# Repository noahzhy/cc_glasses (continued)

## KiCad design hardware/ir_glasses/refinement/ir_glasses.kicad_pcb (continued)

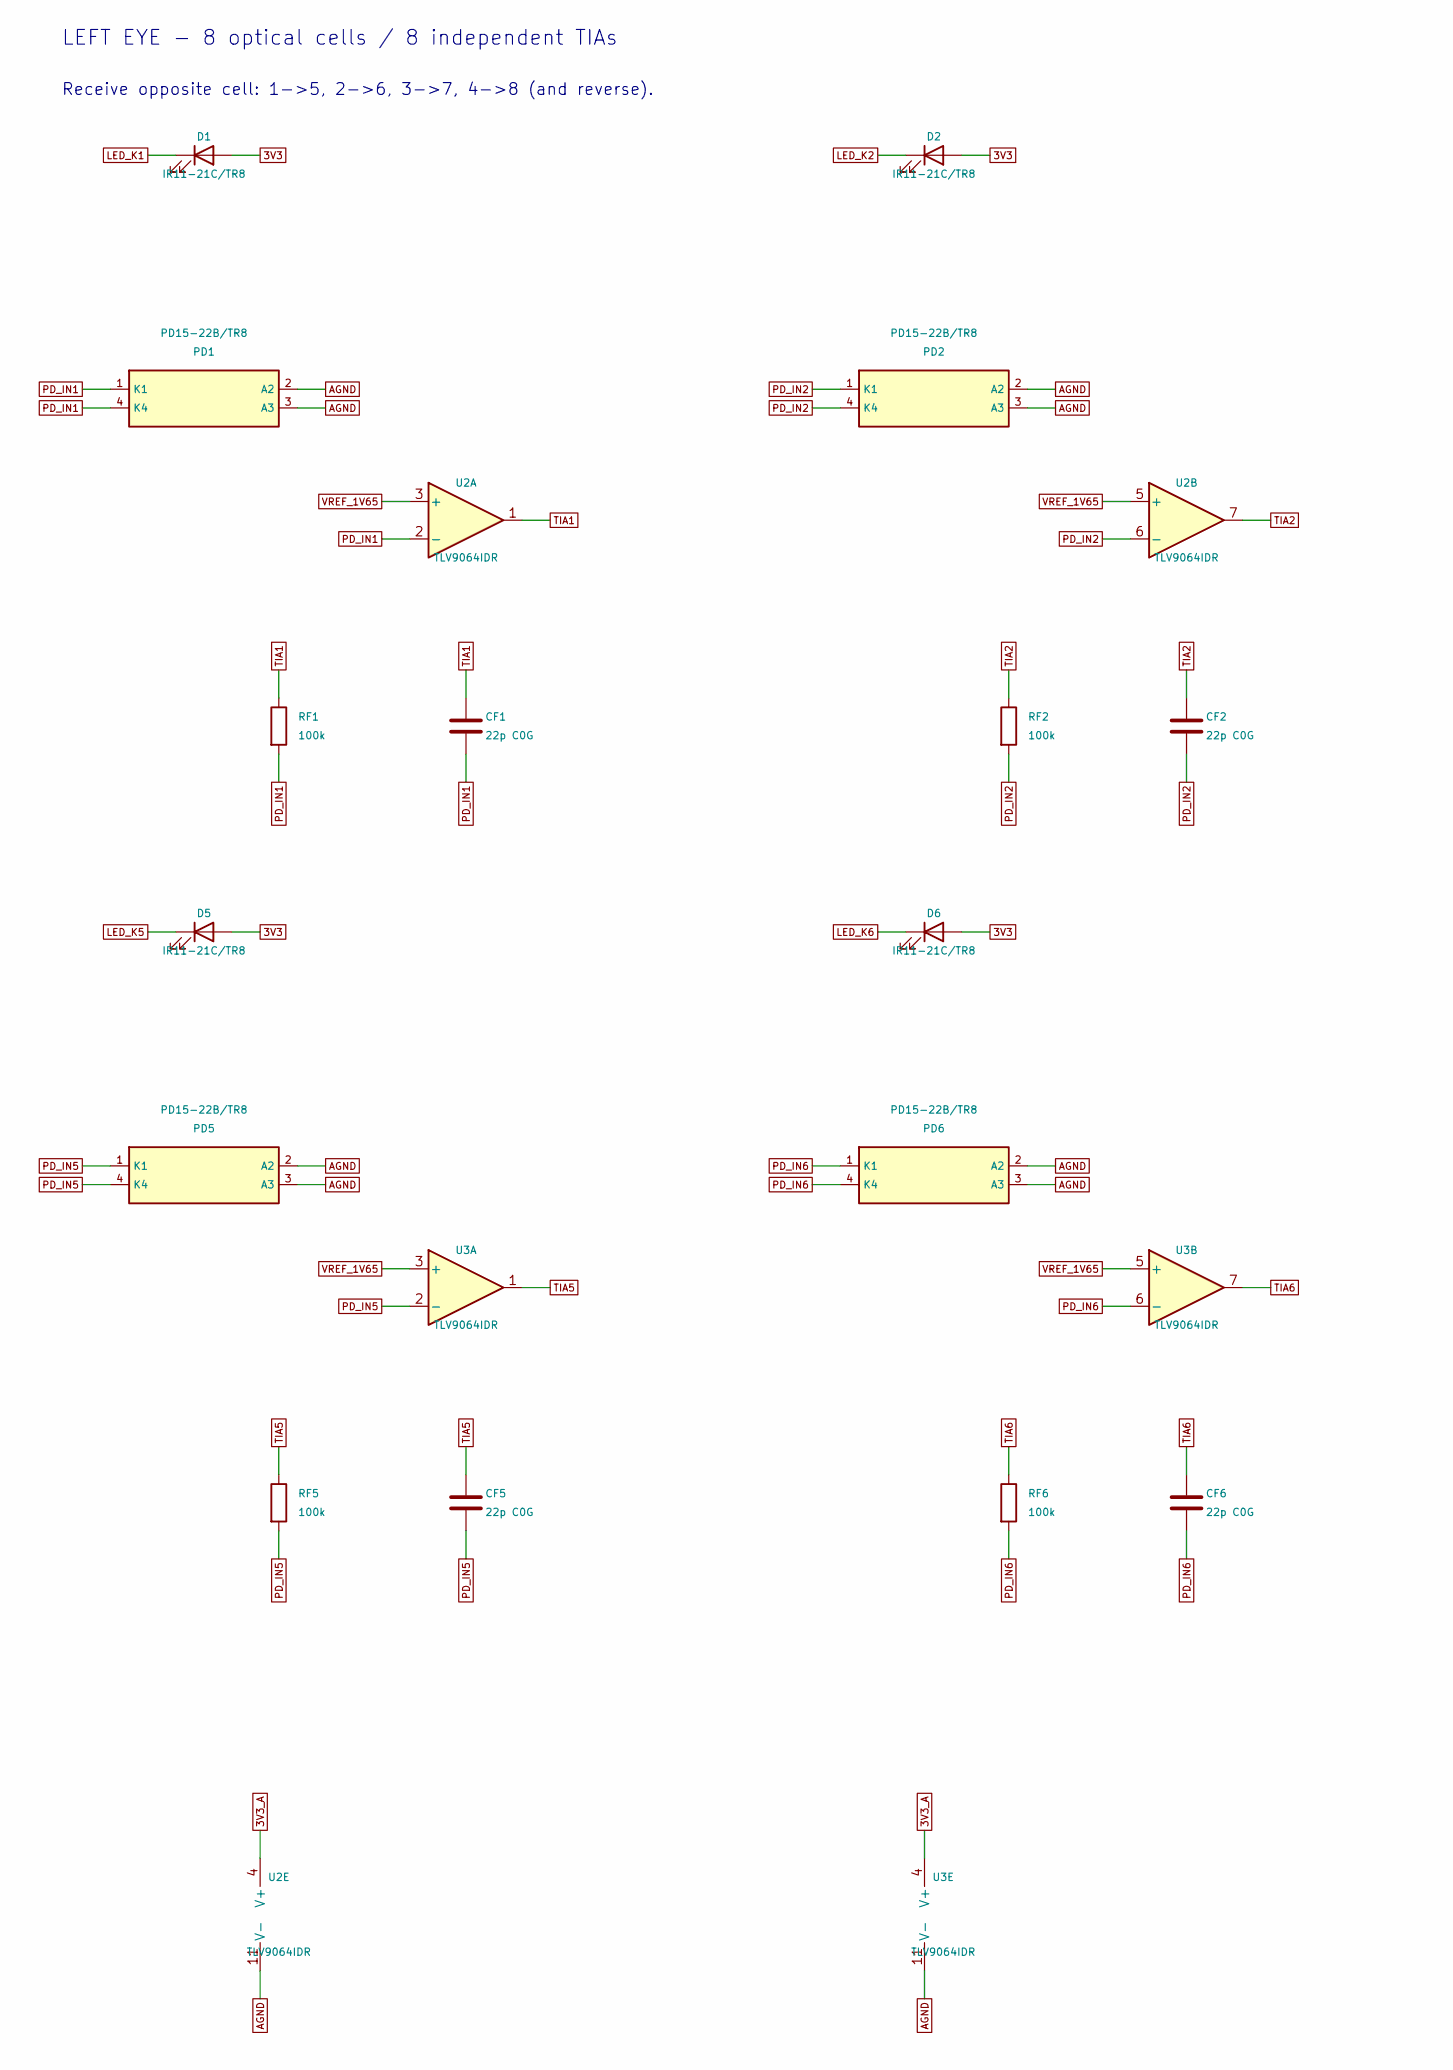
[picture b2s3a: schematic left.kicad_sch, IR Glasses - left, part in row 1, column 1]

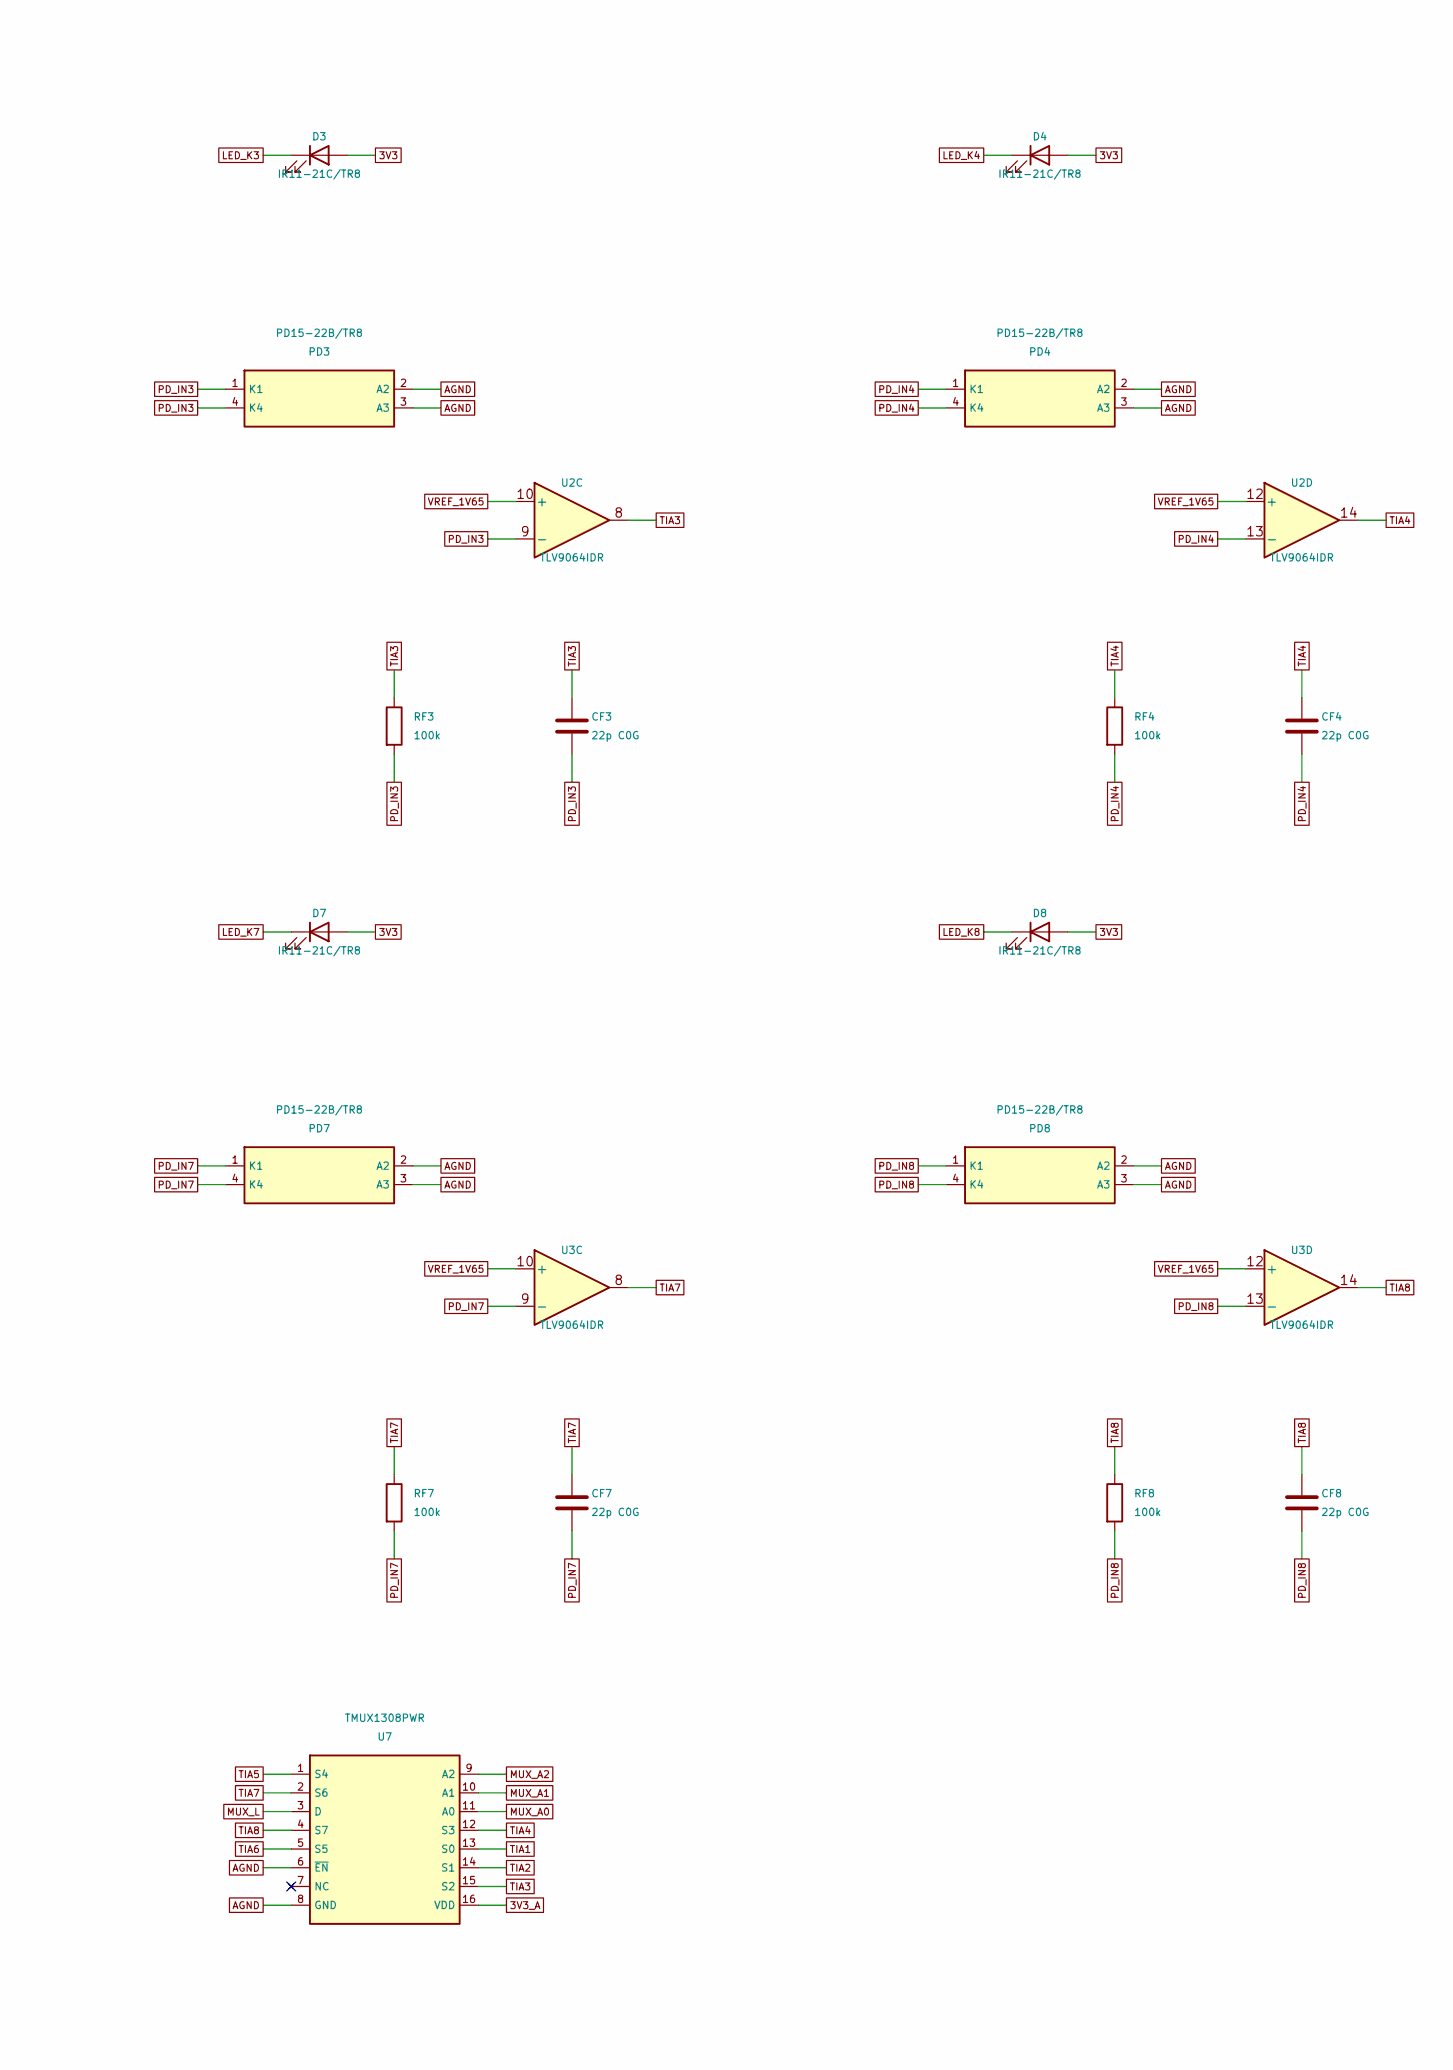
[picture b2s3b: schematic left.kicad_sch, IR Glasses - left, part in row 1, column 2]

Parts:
CF1, CF2, CF3, CF4, CF5, CF6, CF7, CF8: 22p C0G; C_0402_1005Metric
D1, D2, D3, D4, D5, D6, D7, D8: IR11-21C/TR8; Everlight_IR11_21C
PD1, PD2, PD3, PD4, PD5, PD6, PD7, PD8: PD15-22B/TR8; Everlight_PD15_22B
RF1, RF2, RF3, RF4, RF5, RF6, RF7, RF8: 100k; R_0402_1005Metric
U2, U3: TLV9064IDR; SOIC-14_3.9x8.7mm_P1.27mm
U7: TMUX1308PWR; TSSOP-16_4.4x5mm_P0.65mm

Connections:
3V3: D1.1 (A), D2.1 (A), D3.1 (A), D4.1 (A), D5.1 (A), D6.1 (A), D7.1 (A), D8.1 (A); also elsewhere on the board
3V3_A: U2.4 (V+), U3.4 (V+), U7.16 (VDD); also elsewhere on the board
AGND: PD1.2 (A2), PD1.3 (A3), PD2.2 (A2), PD2.3 (A3), PD3.2 (A2), PD3.3 (A3), PD4.2 (A2), PD4.3 (A3), PD5.2 (A2), PD5.3 (A3), PD6.2 (A2), PD6.3 (A3), PD7.2 (A2), PD7.3 (A3), PD8.2 (A2), PD8.3 (A3), U2.11 (V-), U3.11 (V-), U7.6 (~EN), U7.8 (GND); also elsewhere on the board
LED_K1: D1.2 (K); also elsewhere on the board
LED_K2: D2.2 (K); also elsewhere on the board
LED_K3: D3.2 (K); also elsewhere on the board
LED_K4: D4.2 (K); also elsewhere on the board
LED_K5: D5.2 (K); also elsewhere on the board
LED_K6: D6.2 (K); also elsewhere on the board
LED_K7: D7.2 (K); also elsewhere on the board
LED_K8: D8.2 (K); also elsewhere on the board
MUX_A0: U7.11 (A0); also elsewhere on the board
MUX_A1: U7.10 (A1); also elsewhere on the board
MUX_A2: U7.9 (A2); also elsewhere on the board
MUX_L: U7.3 (D); also elsewhere on the board
PD_IN1: CF1.2, PD1.1 (K1), PD1.4 (K4), RF1.2, U2.2 (-)
PD_IN2: CF2.2, PD2.1 (K1), PD2.4 (K4), RF2.2, U2.6 (-)
PD_IN3: CF3.2, PD3.1 (K1), PD3.4 (K4), RF3.2, U2.9 (-)
PD_IN4: CF4.2, PD4.1 (K1), PD4.4 (K4), RF4.2, U2.13 (-)
PD_IN5: CF5.2, PD5.1 (K1), PD5.4 (K4), RF5.2, U3.2 (-)
PD_IN6: CF6.2, PD6.1 (K1), PD6.4 (K4), RF6.2, U3.6 (-)
PD_IN7: CF7.2, PD7.1 (K1), PD7.4 (K4), RF7.2, U3.9 (-)
PD_IN8: CF8.2, PD8.1 (K1), PD8.4 (K4), RF8.2, U3.13 (-)
TIA1: CF1.1, RF1.1, U2.1, U7.13 (S0)
TIA2: CF2.1, RF2.1, U2.7, U7.14 (S1)
TIA3: CF3.1, RF3.1, U2.8, U7.15 (S2)
TIA4: CF4.1, RF4.1, U2.14, U7.12 (S3)
TIA5: CF5.1, RF5.1, U3.1, U7.1 (S4)
TIA6: CF6.1, RF6.1, U3.7, U7.5 (S5)
TIA7: CF7.1, RF7.1, U3.8, U7.2 (S6)
TIA8: CF8.1, RF8.1, U3.14, U7.4 (S7)
VREF_1V65: U2.3 (+), U2.5 (+), U2.10 (+), U2.12 (+), U3.3 (+), U3.5 (+), U3.10 (+), U3.12 (+); also elsewhere on the board

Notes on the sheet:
LEFT EYE - 8 optical cells / 8 independent TIAs
Receive opposite cell: 1->5, 2->6, 3->7, 4->8 (and reverse).

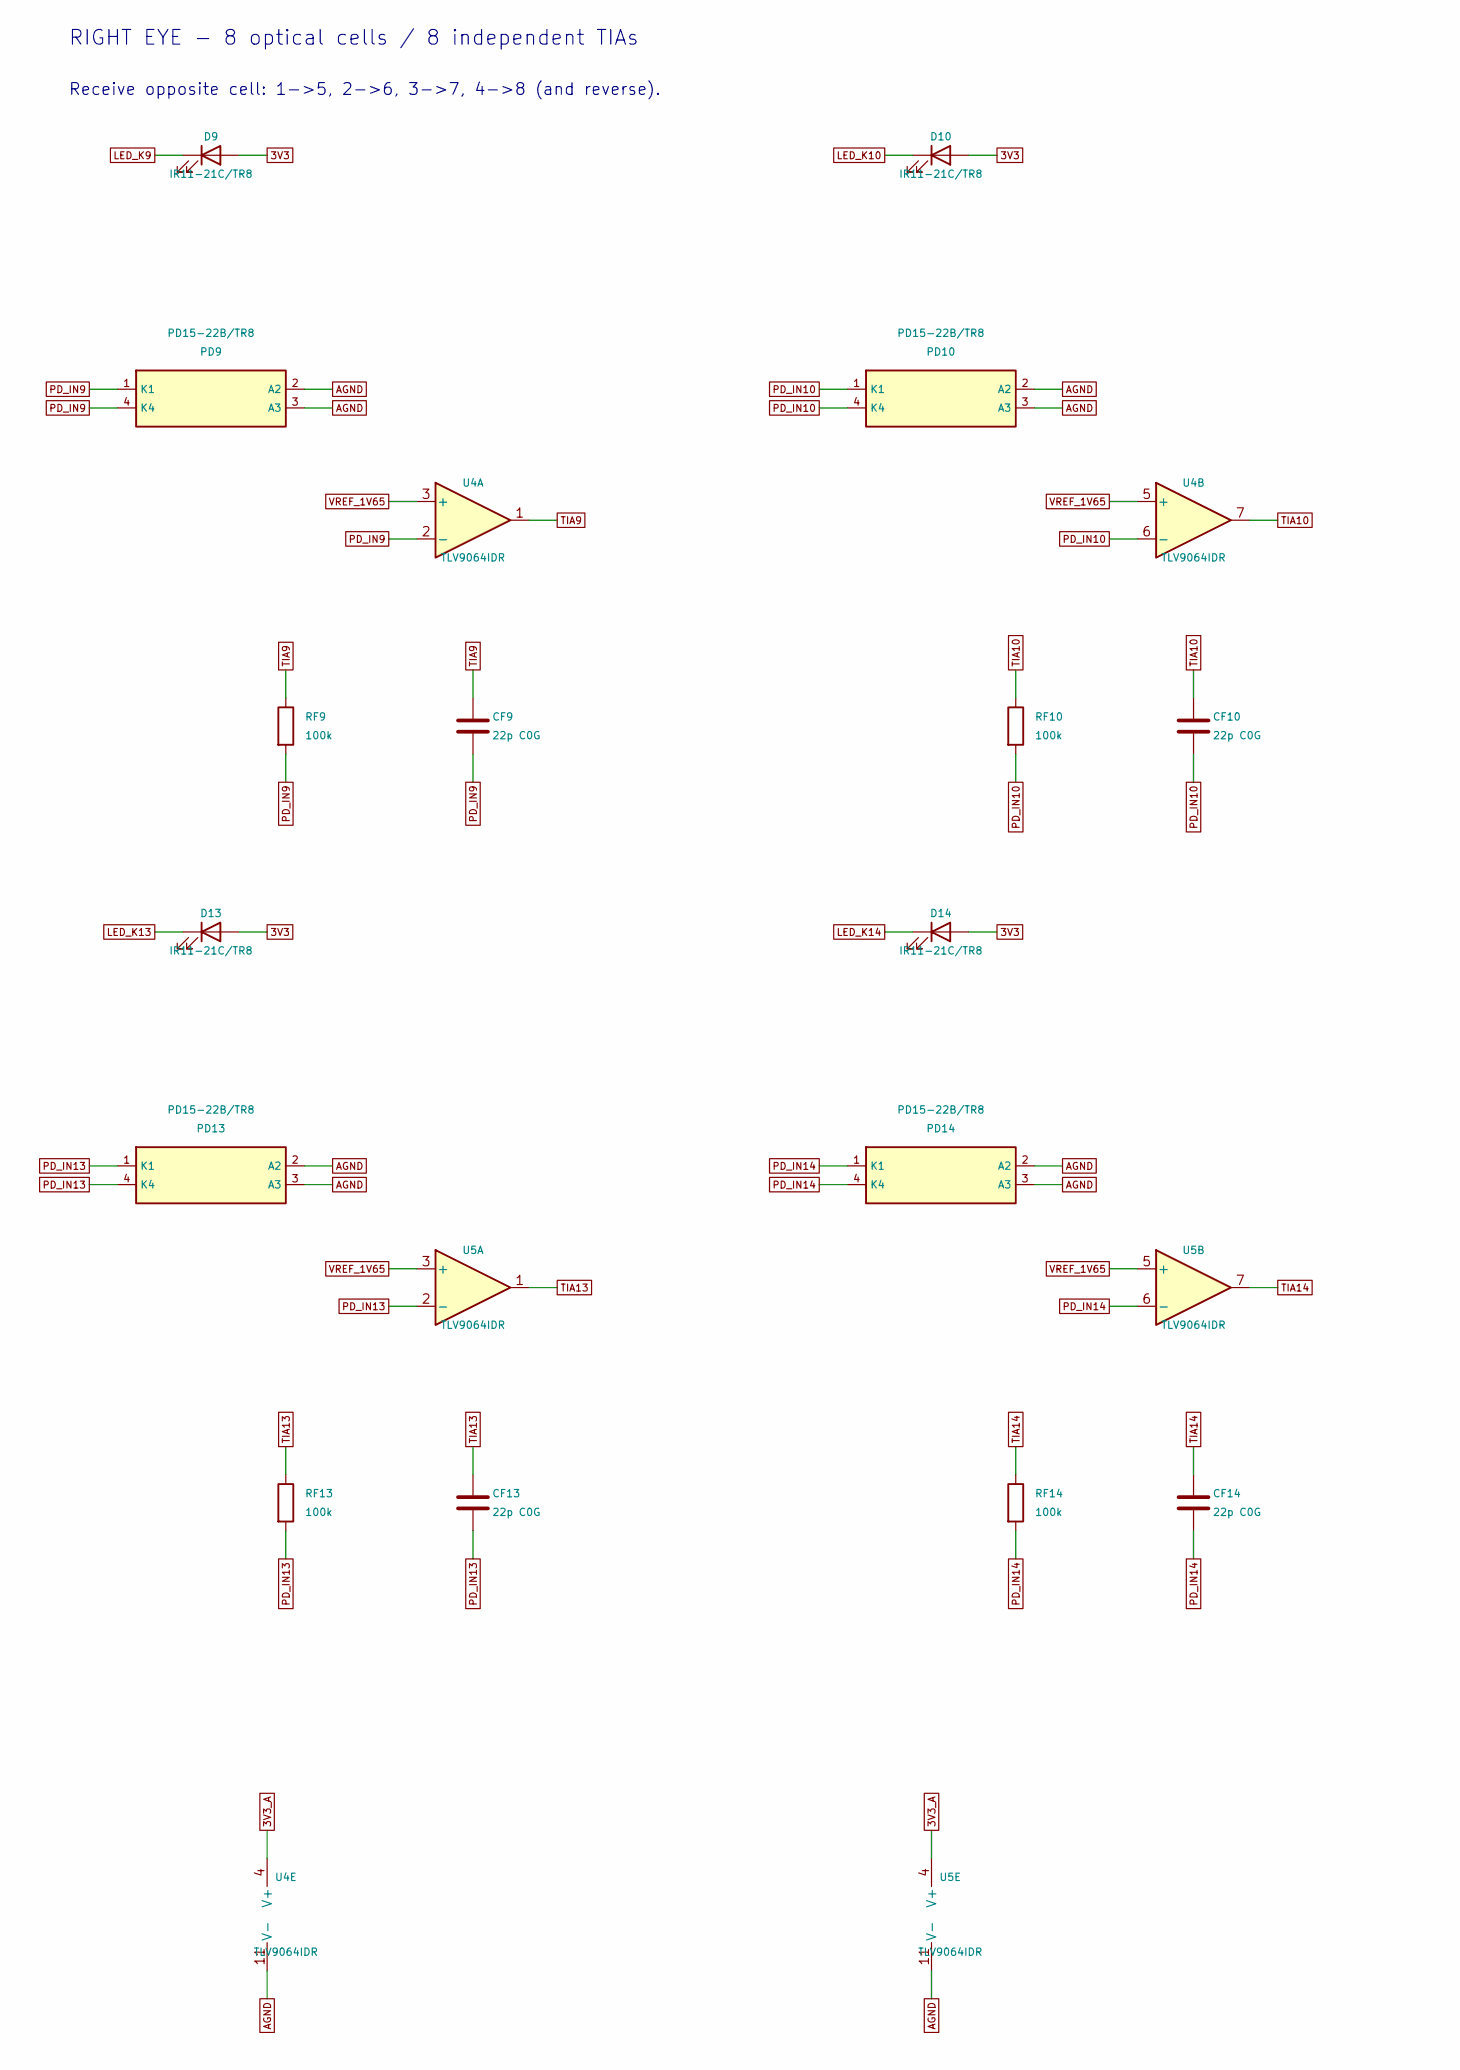
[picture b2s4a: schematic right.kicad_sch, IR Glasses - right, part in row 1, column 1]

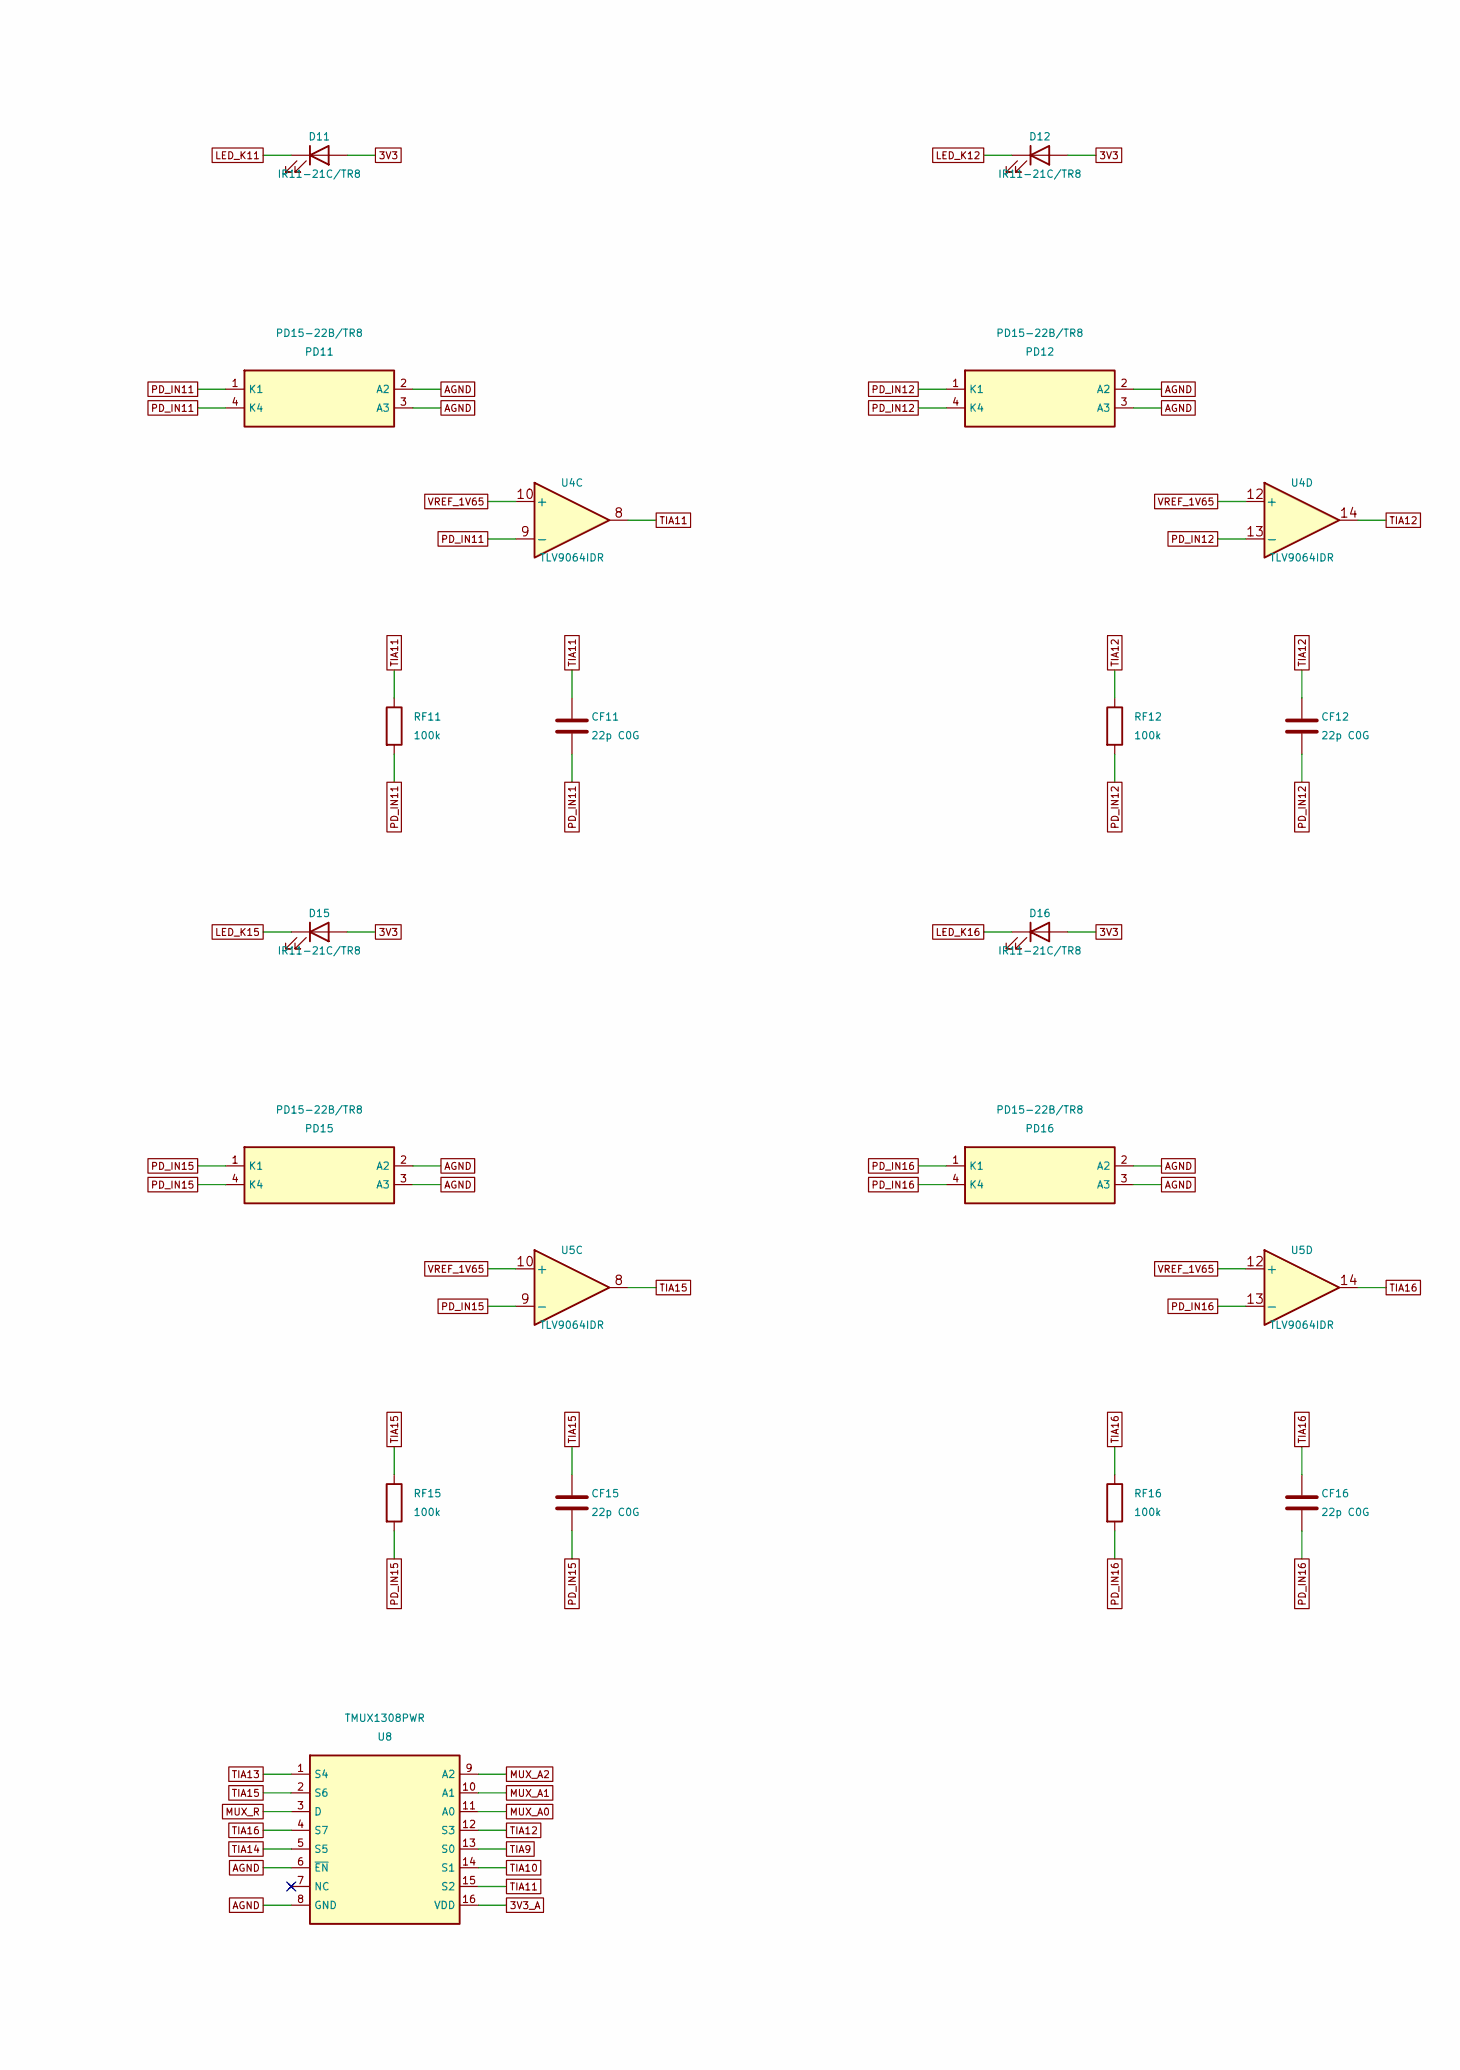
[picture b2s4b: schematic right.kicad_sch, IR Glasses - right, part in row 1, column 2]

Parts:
CF9, CF10, CF11, CF12, CF13, CF14, CF15, CF16: 22p C0G; C_0402_1005Metric
D9, D10, D11, D12, D13, D14, D15, D16: IR11-21C/TR8; Everlight_IR11_21C
PD9, PD10, PD11, PD12, PD13, PD14, PD15, PD16: PD15-22B/TR8; Everlight_PD15_22B
RF9, RF10, RF11, RF12, RF13, RF14, RF15, RF16: 100k; R_0402_1005Metric
U4, U5: TLV9064IDR; SOIC-14_3.9x8.7mm_P1.27mm
U8: TMUX1308PWR; TSSOP-16_4.4x5mm_P0.65mm

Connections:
3V3: D9.1 (A), D10.1 (A), D11.1 (A), D12.1 (A), D13.1 (A), D14.1 (A), D15.1 (A), D16.1 (A); also elsewhere on the board
3V3_A: U4.4 (V+), U5.4 (V+), U8.16 (VDD); also elsewhere on the board
AGND: PD9.2 (A2), PD9.3 (A3), PD10.2 (A2), PD10.3 (A3), PD11.2 (A2), PD11.3 (A3), PD12.2 (A2), PD12.3 (A3), PD13.2 (A2), PD13.3 (A3), PD14.2 (A2), PD14.3 (A3), PD15.2 (A2), PD15.3 (A3), PD16.2 (A2), PD16.3 (A3), U4.11 (V-), U5.11 (V-), U8.6 (~EN), U8.8 (GND); also elsewhere on the board
LED_K9: D9.2 (K); also elsewhere on the board
LED_K10: D10.2 (K); also elsewhere on the board
LED_K11: D11.2 (K); also elsewhere on the board
LED_K12: D12.2 (K); also elsewhere on the board
LED_K13: D13.2 (K); also elsewhere on the board
LED_K14: D14.2 (K); also elsewhere on the board
LED_K15: D15.2 (K); also elsewhere on the board
LED_K16: D16.2 (K); also elsewhere on the board
MUX_A0: U8.11 (A0); also elsewhere on the board
MUX_A1: U8.10 (A1); also elsewhere on the board
MUX_A2: U8.9 (A2); also elsewhere on the board
MUX_R: U8.3 (D); also elsewhere on the board
PD_IN9: CF9.2, PD9.1 (K1), PD9.4 (K4), RF9.2, U4.2 (-)
PD_IN10: CF10.2, PD10.1 (K1), PD10.4 (K4), RF10.2, U4.6 (-)
PD_IN11: CF11.2, PD11.1 (K1), PD11.4 (K4), RF11.2, U4.9 (-)
PD_IN12: CF12.2, PD12.1 (K1), PD12.4 (K4), RF12.2, U4.13 (-)
PD_IN13: CF13.2, PD13.1 (K1), PD13.4 (K4), RF13.2, U5.2 (-)
PD_IN14: CF14.2, PD14.1 (K1), PD14.4 (K4), RF14.2, U5.6 (-)
PD_IN15: CF15.2, PD15.1 (K1), PD15.4 (K4), RF15.2, U5.9 (-)
PD_IN16: CF16.2, PD16.1 (K1), PD16.4 (K4), RF16.2, U5.13 (-)
TIA9: CF9.1, RF9.1, U4.1, U8.13 (S0)
TIA10: CF10.1, RF10.1, U4.7, U8.14 (S1)
TIA11: CF11.1, RF11.1, U4.8, U8.15 (S2)
TIA12: CF12.1, RF12.1, U4.14, U8.12 (S3)
TIA13: CF13.1, RF13.1, U5.1, U8.1 (S4)
TIA14: CF14.1, RF14.1, U5.7, U8.5 (S5)
TIA15: CF15.1, RF15.1, U5.8, U8.2 (S6)
TIA16: CF16.1, RF16.1, U5.14, U8.4 (S7)
VREF_1V65: U4.3 (+), U4.5 (+), U4.10 (+), U4.12 (+), U5.3 (+), U5.5 (+), U5.10 (+), U5.12 (+); also elsewhere on the board

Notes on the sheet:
RIGHT EYE - 8 optical cells / 8 independent TIAs
Receive opposite cell: 1->5, 2->6, 3->7, 4->8 (and reverse).

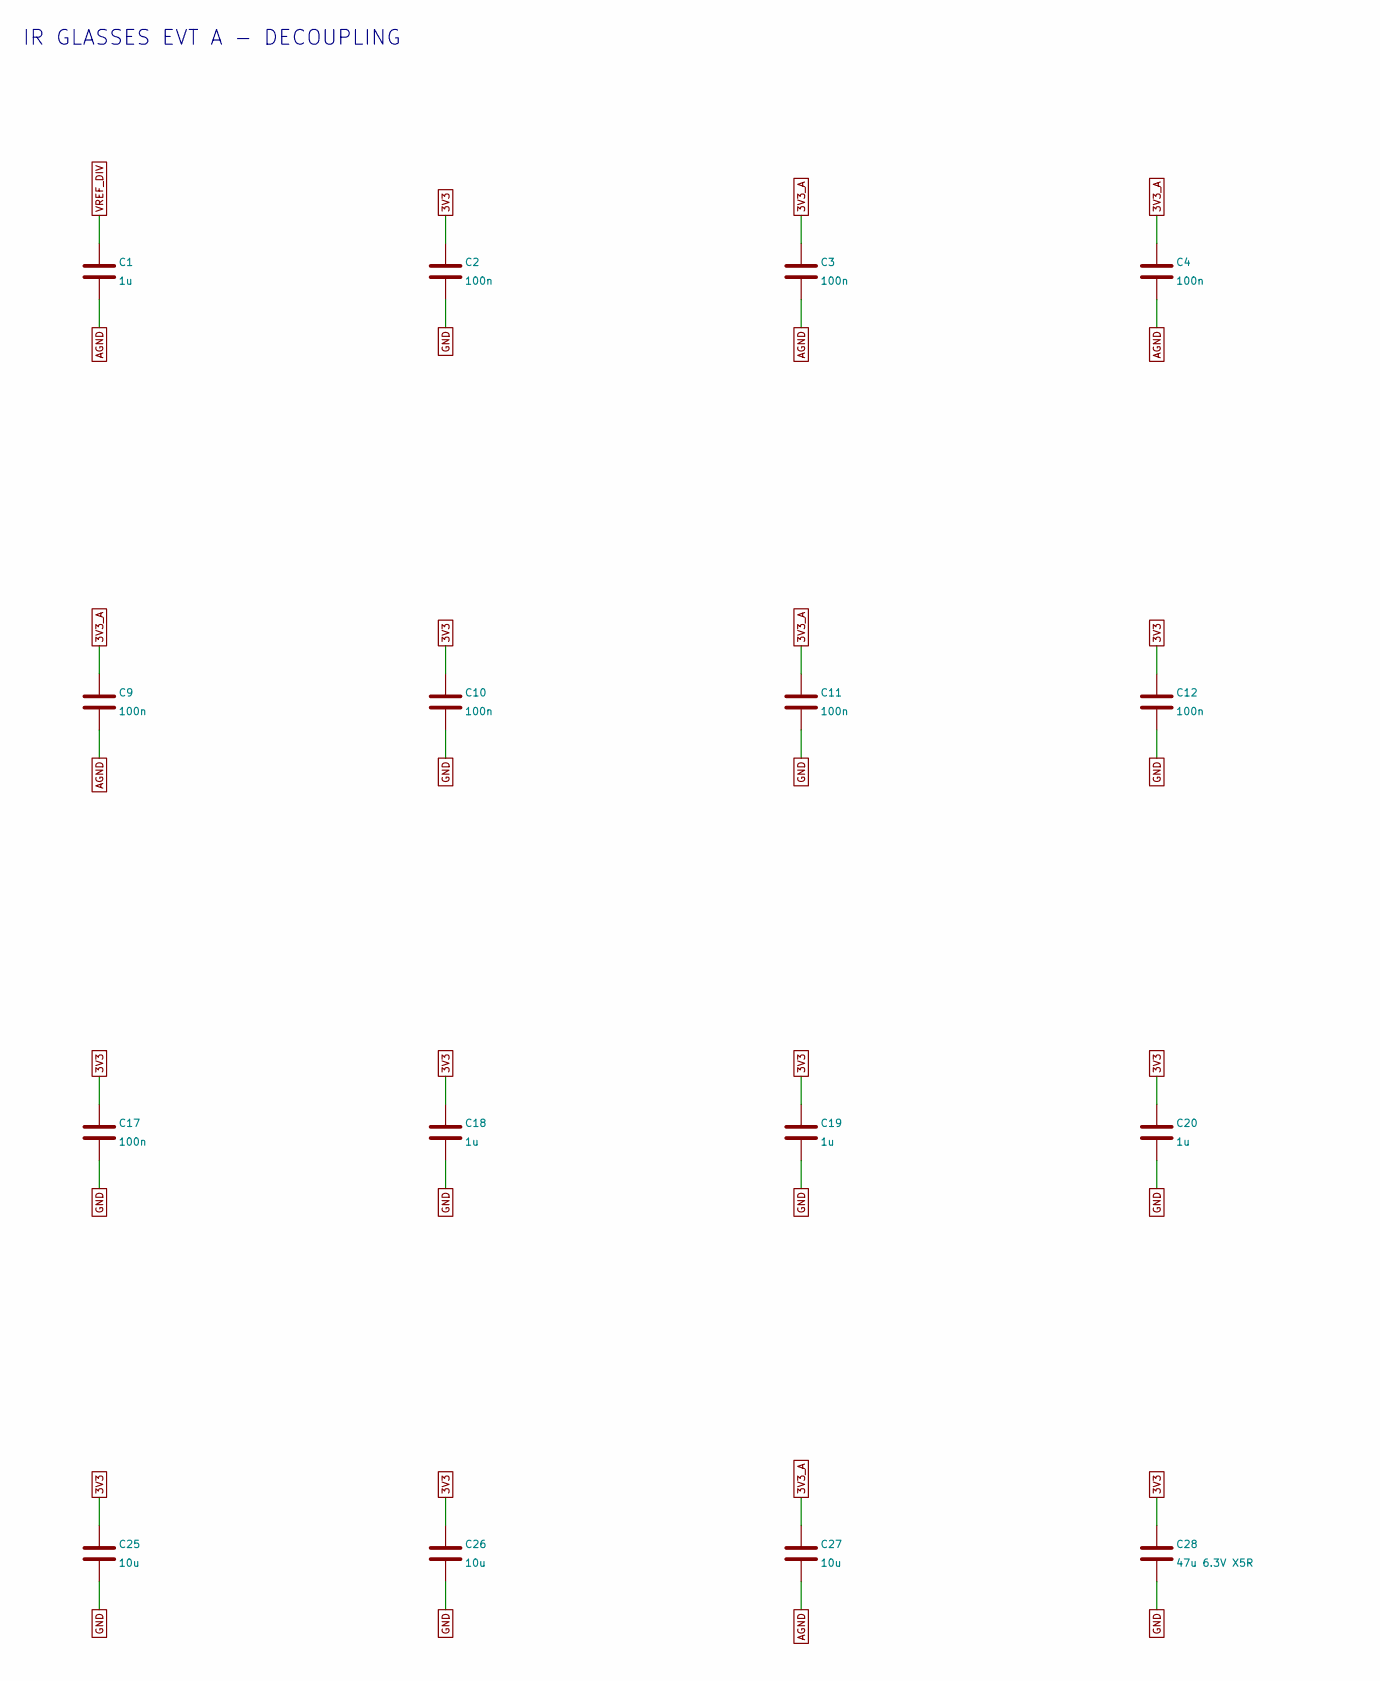
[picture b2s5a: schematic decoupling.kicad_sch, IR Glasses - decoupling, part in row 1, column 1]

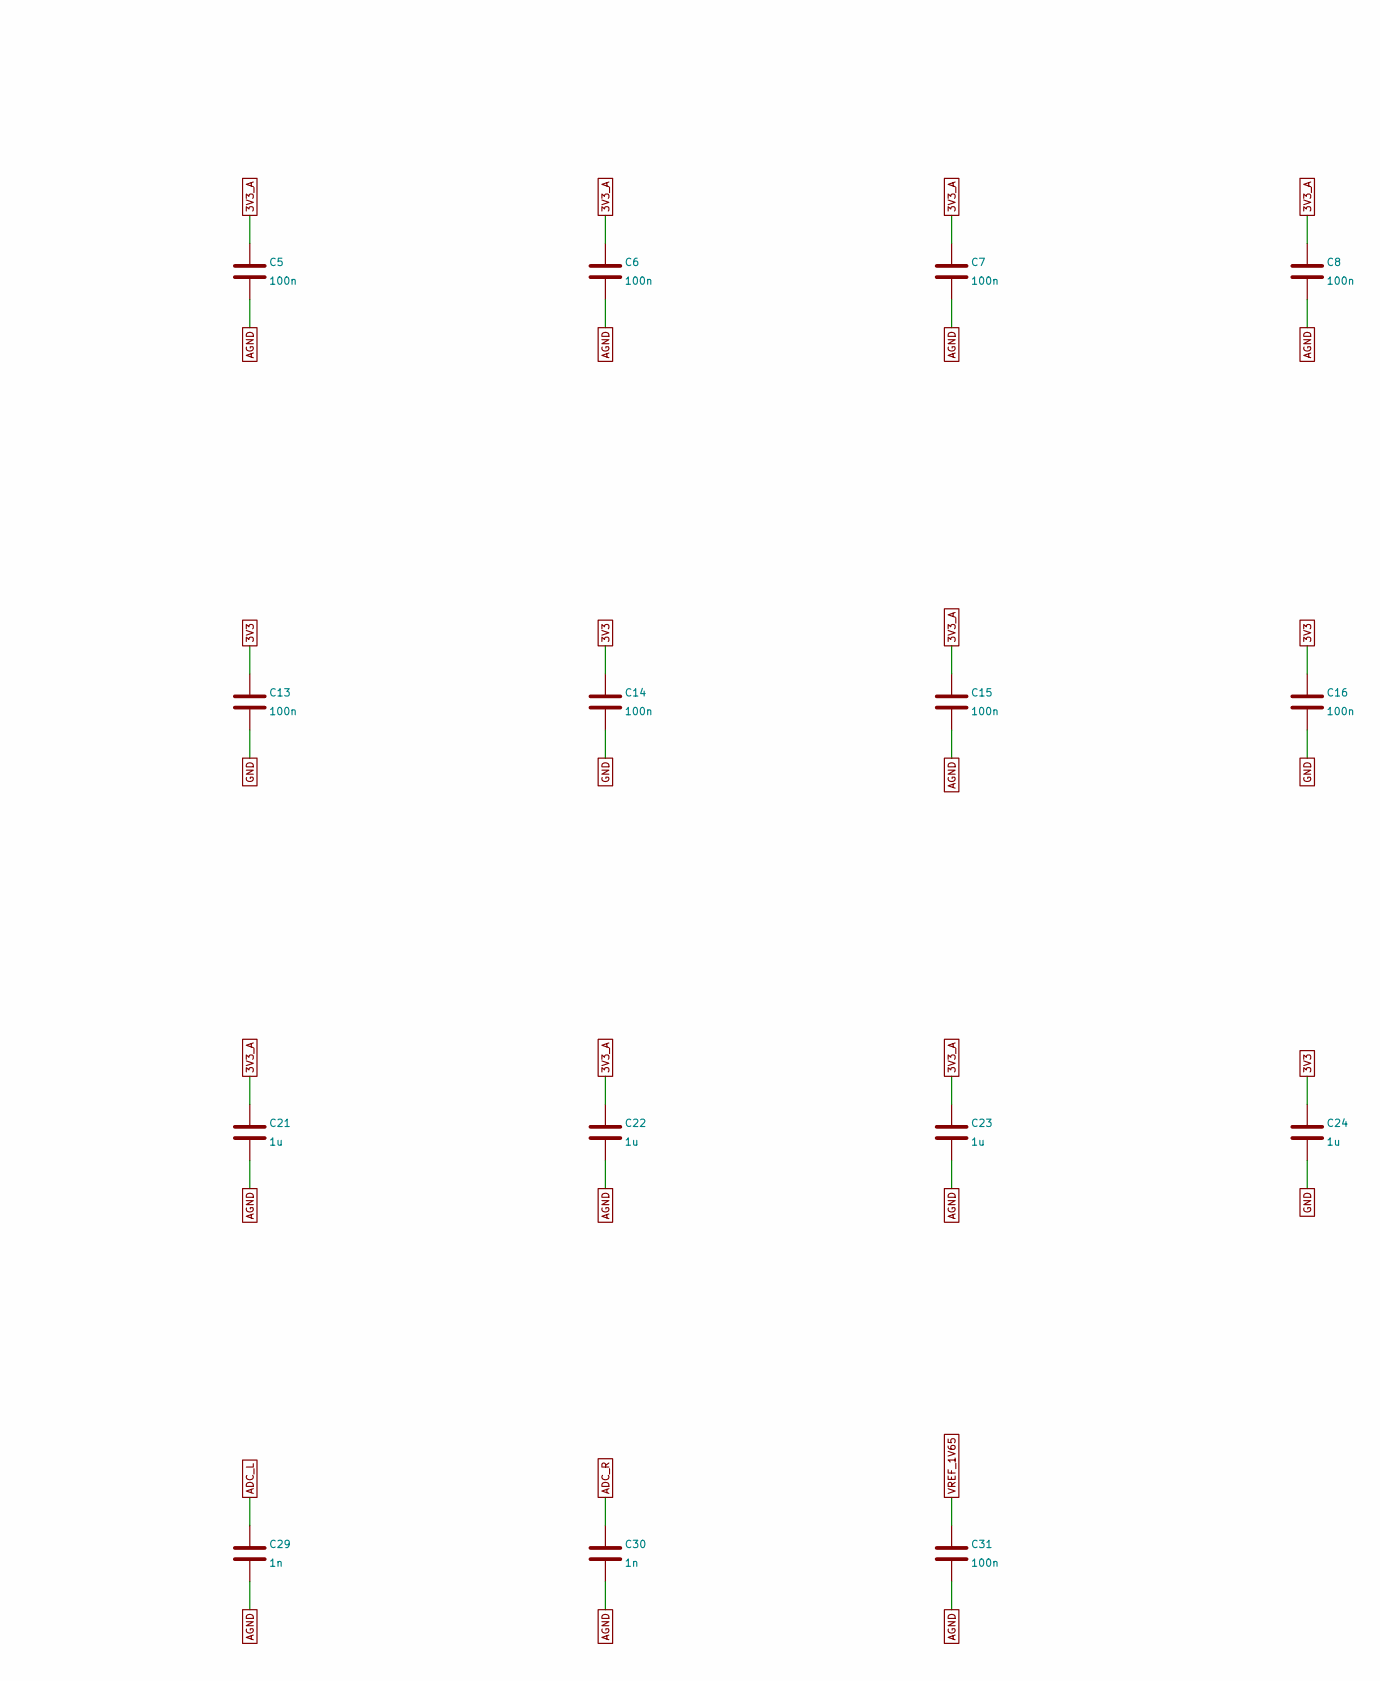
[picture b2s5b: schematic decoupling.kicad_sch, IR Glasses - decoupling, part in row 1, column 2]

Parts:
C1, C18, C19, C20, C21, C22, C23, C24: 1u; C_0402_1005Metric
C2, C3, C4, C5, C6, C7, C8, C9, C10, C11, C12, C13, C14, C15, C16, C17, C31: 100n; C_0402_1005Metric
C25, C26, C27: 10u; C_0603_1608Metric
C28: 47u 6.3V X5R; C_1210_3225Metric
C29, C30: 1n; C_0402_1005Metric

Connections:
3V3: C2.1, C10.1, C12.1, C13.1, C14.1, C16.1, C17.1, C18.1, C19.1, C20.1, C24.1, C25.1, C26.1, C28.1; also elsewhere on the board
3V3_A: C3.1, C4.1, C5.1, C6.1, C7.1, C8.1, C9.1, C11.1, C15.1, C21.1, C22.1, C23.1, C27.1; also elsewhere on the board
ADC_L: C29.1; also elsewhere on the board
ADC_R: C30.1; also elsewhere on the board
AGND: C1.2, C3.2, C4.2, C5.2, C6.2, C7.2, C8.2, C9.2, C15.2, C21.2, C22.2, C23.2, C27.2, C29.2, C30.2, C31.2; also elsewhere on the board
GND: C2.2, C10.2, C11.2, C12.2, C13.2, C14.2, C16.2, C17.2, C18.2, C19.2, C20.2, C24.2, C25.2, C26.2, C28.2; also elsewhere on the board
VREF_1V65: C31.1; also elsewhere on the board
VREF_DIV: C1.1; also elsewhere on the board

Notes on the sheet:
IR GLASSES EVT A - DECOUPLING
